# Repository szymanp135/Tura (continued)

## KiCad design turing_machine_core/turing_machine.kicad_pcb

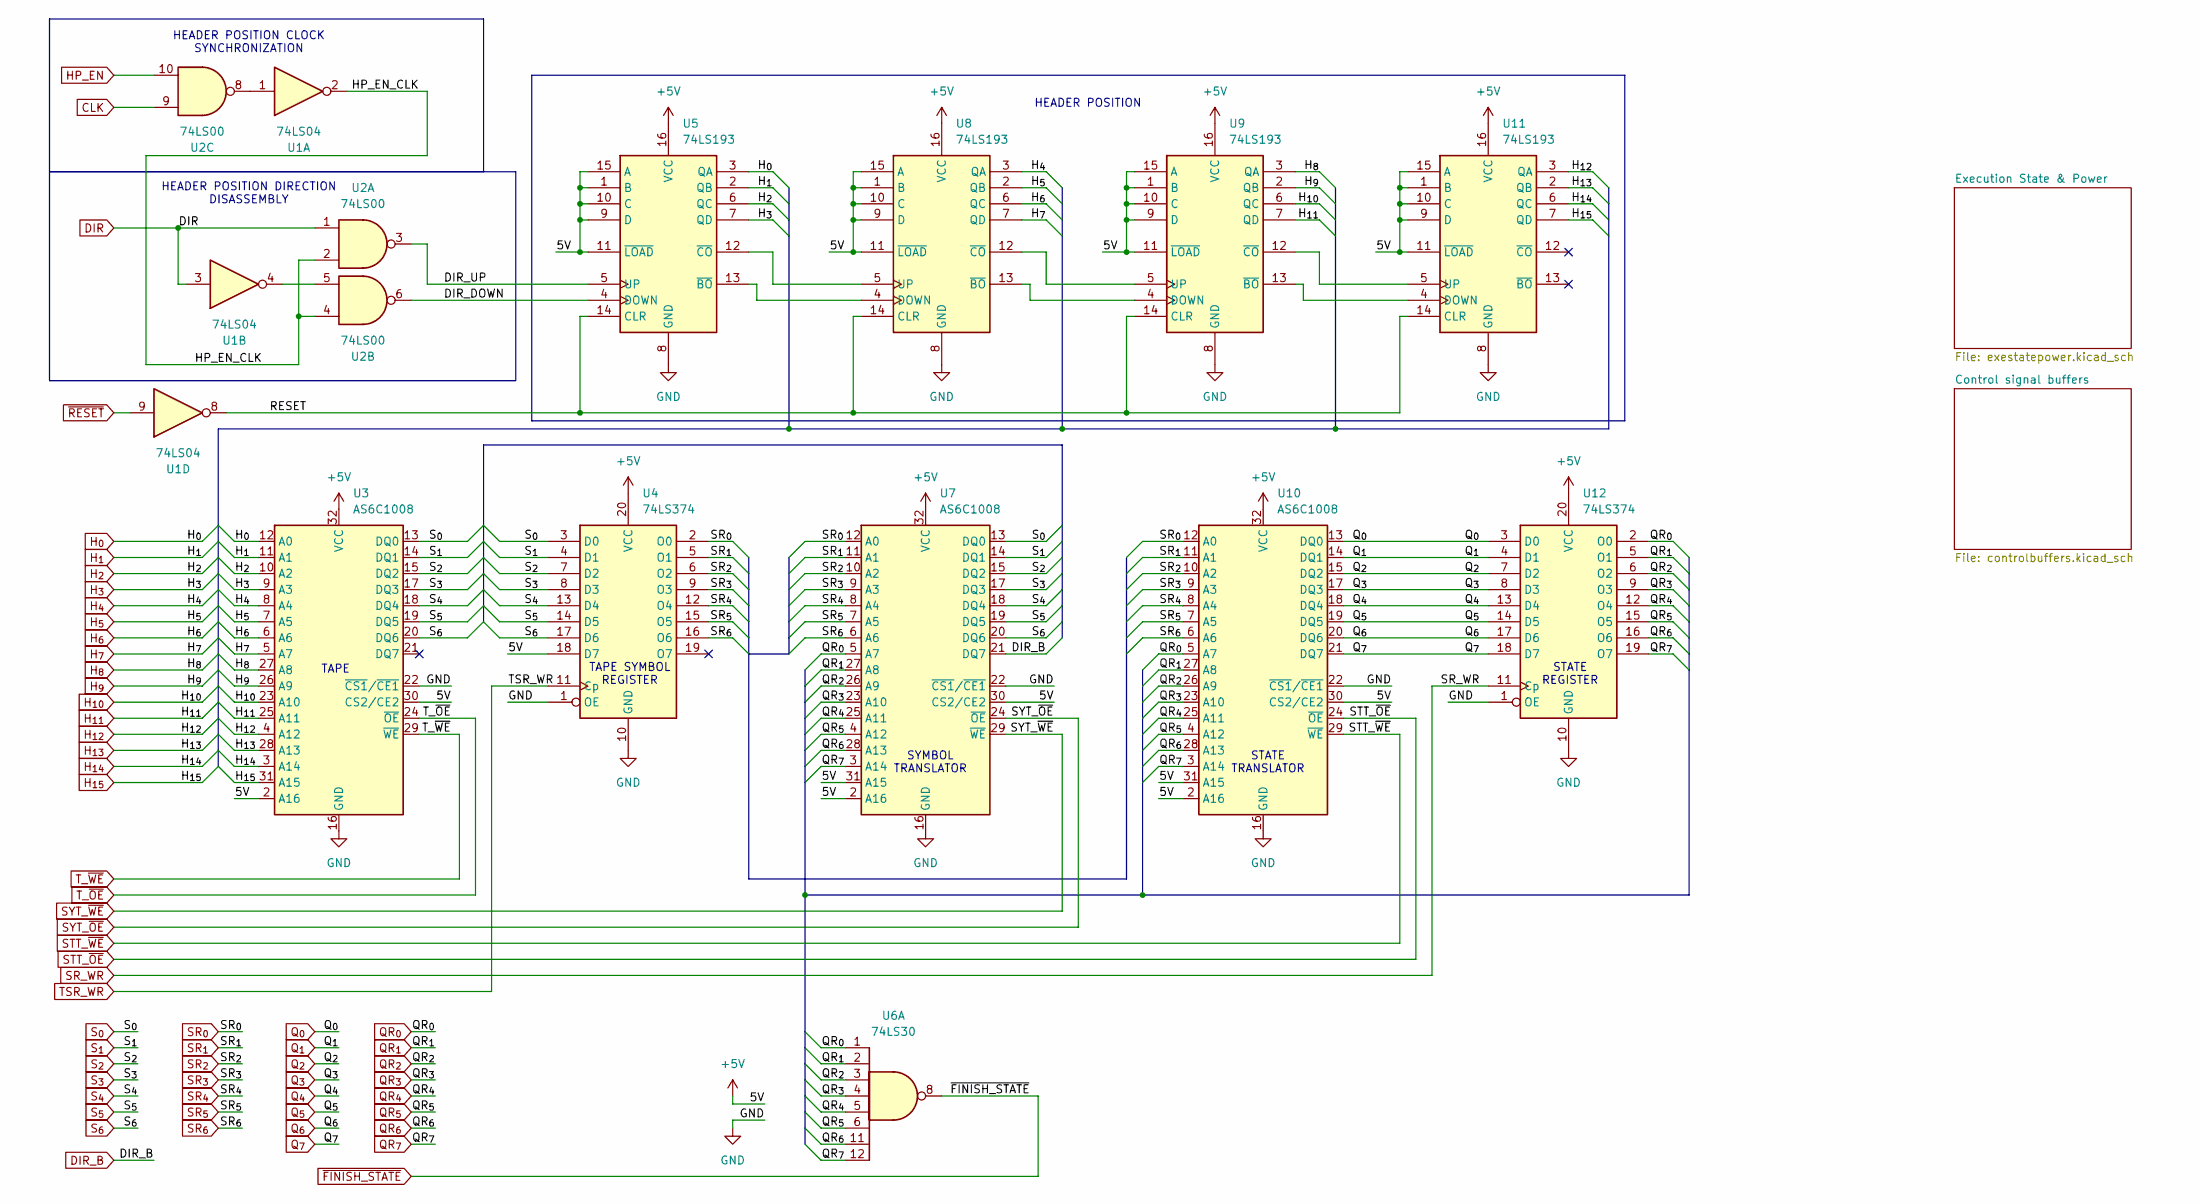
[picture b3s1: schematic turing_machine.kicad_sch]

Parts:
U1: 74LS04; DIP-14_W7.62mm
U2: 74LS00; DIP-14_W7.62mm
U3, U7, U10: AS6C1008; DIP-32_W15.24mm
U4, U12: 74LS374; DIP-20_W7.62mm
U5, U8, U9, U11: 74LS193; DIP-16_W7.62mm
U6: 74LS30; DIP-14_W7.62mm

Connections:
+5V: U3.2 (A16), U3.30 (CS2/CE2), U3.32 (VCC), U4.18 (D7), U4.20 (VCC), U5.1 (B), U5.9 (D), U5.10 (C), U5.11 (~LOAD), U5.15 (A), U5.16 (VCC), U7.2 (A16), U7.30 (CS2/CE2), U7.31 (A15), U7.32 (VCC), U8.1 (B), U8.9 (D), U8.10 (C), U8.11 (~LOAD), U8.15 (A), U8.16 (VCC), U9.1 (B), U9.9 (D), U9.10 (C), U9.11 (~LOAD), U9.15 (A), U9.16 (VCC), U10.2 (A16), U10.30 (CS2/CE2), U10.31 (A15), U10.32 (VCC), U11.1 (B), U11.9 (D), U11.10 (C), U11.11 (~LOAD), U11.15 (A), U11.16 (VCC), U12.20 (VCC); also elsewhere on the board
/DIR_DOWN: U2.6, U5.4 (DOWN)
/DIR_UP: U2.3, U5.5 (UP)
/HP_EN_CLK: U1.2, U2.2, U2.4
/RESET: U1.8, U5.14 (CLR), U8.14 (CLR), U9.14 (CLR), U11.14 (CLR)
CLK: U2.9; also elsewhere on the board
DIR: U1.3, U2.1; also elsewhere on the board
DIR_B: U7.21 (DQ7); also elsewhere on the board
GND: U3.16 (GND), U3.22 (~CS1/~CE1), U4.1 (OE), U4.10 (GND), U5.8 (GND), U7.16 (GND), U7.22 (~CS1/~CE1), U8.8 (GND), U9.8 (GND), U10.16 (GND), U10.22 (~CS1/~CE1), U11.8 (GND), U12.1 (OE), U12.10 (GND); also elsewhere on the board
HP_EN: U2.10, U4.11 (Cp); also elsewhere on the board
H_{0}: U3.12 (A0), U5.3 (QA); also elsewhere on the board
H_{1}: U3.11 (A1), U5.2 (QB); also elsewhere on the board
H_{2}: U3.10 (A2), U5.6 (QC); also elsewhere on the board
H_{3}: U3.9 (A3), U5.7 (QD); also elsewhere on the board
H_{4}: U3.8 (A4), U8.3 (QA); also elsewhere on the board
H_{5}: U3.7 (A5), U8.2 (QB); also elsewhere on the board
H_{6}: U3.6 (A6), U8.6 (QC); also elsewhere on the board
H_{7}: U3.5 (A7), U8.7 (QD); also elsewhere on the board
H_{8}: U3.27 (A8), U9.3 (QA); also elsewhere on the board
H_{9}: U3.26 (A9), U9.2 (QB); also elsewhere on the board
H_{10}: U3.23 (A10), U9.6 (QC); also elsewhere on the board
H_{11}: U3.25 (A11), U9.7 (QD); also elsewhere on the board
H_{12}: U3.4 (A12), U11.3 (QA); also elsewhere on the board
H_{13}: U3.28 (A13), U11.2 (QB); also elsewhere on the board
H_{14}: U3.3 (A14), U11.6 (QC); also elsewhere on the board
H_{15}: U3.31 (A15), U11.7 (QD); also elsewhere on the board
unnamed: U1.1, U2.8
unnamed: U1.4, U2.5
unnamed: U5.13 (~BO), U8.4 (DOWN)
unnamed: U5.12 (~CO), U8.5 (UP)
unnamed: U8.13 (~BO), U9.4 (DOWN)
unnamed: U8.12 (~CO), U9.5 (UP)
unnamed: U9.13 (~BO), U11.4 (DOWN)
unnamed: U9.12 (~CO), U11.5 (UP)
QR_{0}: U6.1, U7.5 (A7), U10.5 (A7), U12.2 (O0); also elsewhere on the board
QR_{1}: U6.2, U7.27 (A8), U10.27 (A8), U12.5 (O1); also elsewhere on the board
QR_{2}: U6.3, U7.26 (A9), U10.26 (A9), U12.6 (O2); also elsewhere on the board
QR_{3}: U6.4, U7.23 (A10), U10.23 (A10), U12.9 (O3); also elsewhere on the board
QR_{4}: U6.5, U7.25 (A11), U10.25 (A11), U12.12 (O4); also elsewhere on the board
QR_{5}: U6.6, U7.4 (A12), U10.4 (A12), U12.15 (O5); also elsewhere on the board
QR_{6}: U6.11, U7.28 (A13), U10.28 (A13), U12.16 (O6); also elsewhere on the board
QR_{7}: U6.12, U7.3 (A14), U10.3 (A14), U12.19 (O7); also elsewhere on the board
Q_{0}: U10.13 (DQ0), U12.3 (D0); also elsewhere on the board
Q_{1}: U10.14 (DQ1), U12.4 (D1); also elsewhere on the board
Q_{2}: U10.15 (DQ2), U12.7 (D2); also elsewhere on the board
Q_{3}: U10.17 (DQ3), U12.8 (D3); also elsewhere on the board
Q_{4}: U10.18 (DQ4), U12.13 (D4); also elsewhere on the board
Q_{5}: U10.19 (DQ5), U12.14 (D5); also elsewhere on the board
Q_{6}: U10.20 (DQ6), U12.17 (D6); also elsewhere on the board
Q_{7}: U10.21 (DQ7), U12.18 (D7); also elsewhere on the board
SR_WR: U12.11 (Cp); also elsewhere on the board
SR_{0}: U4.2 (O0), U7.12 (A0), U10.12 (A0); also elsewhere on the board
SR_{1}: U4.5 (O1), U7.11 (A1), U10.11 (A1); also elsewhere on the board
SR_{2}: U4.6 (O2), U7.10 (A2), U10.10 (A2); also elsewhere on the board
SR_{3}: U4.9 (O3), U7.9 (A3), U10.9 (A3); also elsewhere on the board
SR_{4}: U4.12 (O4), U7.8 (A4), U10.8 (A4); also elsewhere on the board
SR_{5}: U4.15 (O5), U7.7 (A5), U10.7 (A5); also elsewhere on the board
SR_{6}: U4.16 (O6), U7.6 (A6), U10.6 (A6); also elsewhere on the board
STT_~OE: U10.24 (~OE); also elsewhere on the board
STT_~WE: U10.29 (~WE); also elsewhere on the board
SYT_~OE: U7.24 (~OE); also elsewhere on the board
SYT_~WE: U7.29 (~WE); also elsewhere on the board
S_{0}: U3.13 (DQ0), U4.3 (D0), U7.13 (DQ0); also elsewhere on the board
S_{1}: U3.14 (DQ1), U4.4 (D1), U7.14 (DQ1); also elsewhere on the board
S_{2}: U3.15 (DQ2), U4.7 (D2), U7.15 (DQ2); also elsewhere on the board
S_{3}: U3.17 (DQ3), U4.8 (D3), U7.17 (DQ3); also elsewhere on the board
S_{4}: U3.18 (DQ4), U4.13 (D4), U7.18 (DQ4); also elsewhere on the board
S_{5}: U3.19 (DQ5), U4.14 (D5), U7.19 (DQ5); also elsewhere on the board
S_{6}: U3.20 (DQ6), U4.17 (D6), U7.20 (DQ6); also elsewhere on the board
T_~OE: U3.24 (~OE); also elsewhere on the board
T_~WE: U3.29 (~WE); also elsewhere on the board
~FINISH_STATE: U6.8; also elsewhere on the board
~RESET: U1.9; also elsewhere on the board

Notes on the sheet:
HEADER POSITION DIRECTION DISASSEMBLY
HEADER POSITION CLOCK SYNCHRONIZATION
STATE TRANSLATOR
TAPE SYMBOL REGISTER
HEADER POSITION
TAPE
STATE REGISTER
SYMBOL TRANSLATOR

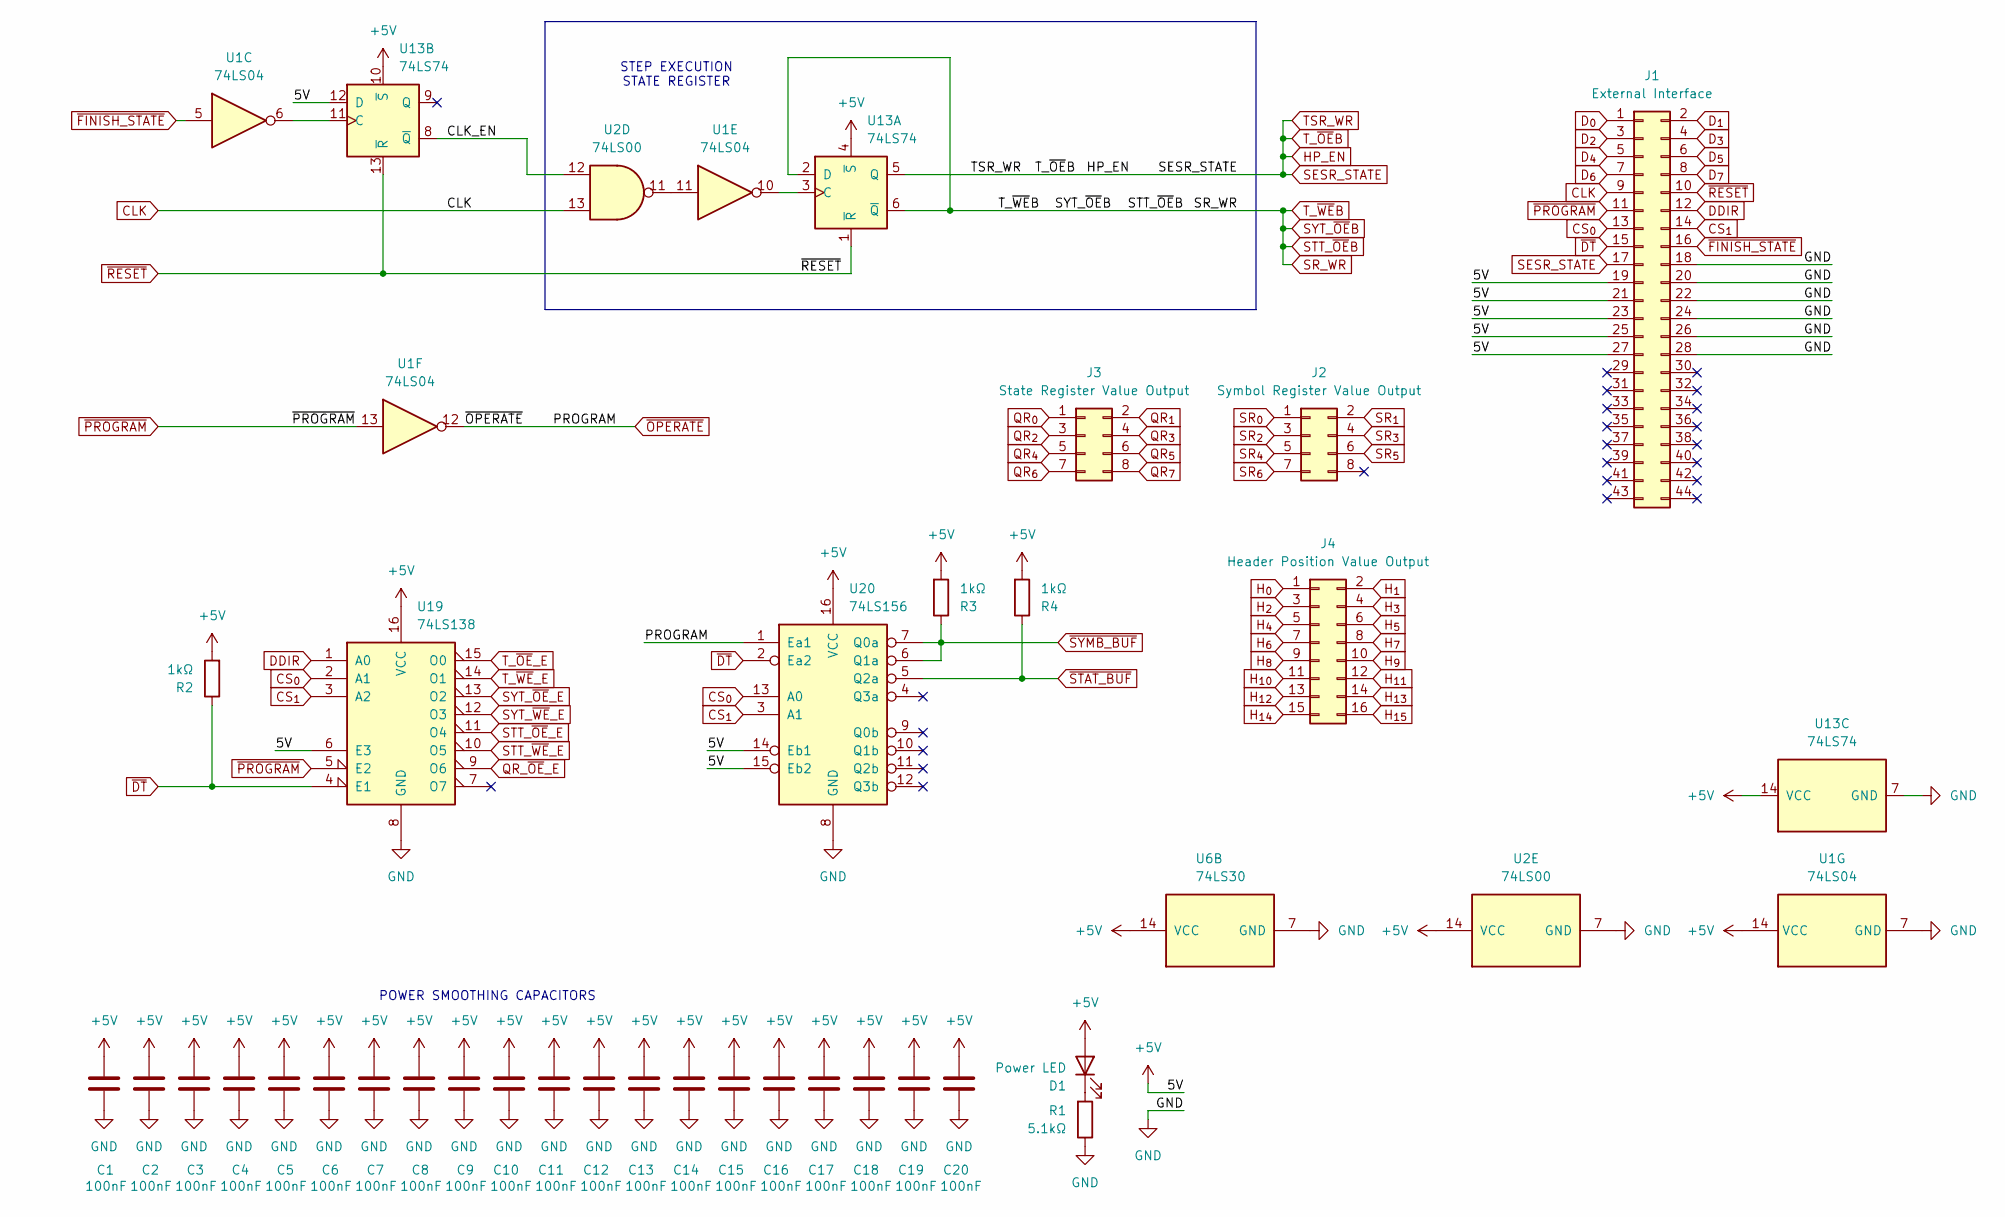
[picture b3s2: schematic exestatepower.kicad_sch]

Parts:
C1, C2, C3, C4, C5, C6, C7, C8, C9, C10, C11, C12, C13, C14, C15, C16, C17, C18, C19, C20: 100nF; C_Disc_D3.8mm_W2.6mm_P2.50mm
D1: Power LED; LED_D5.0mm
J1: External Interface; Connector_Edge_2x22pin_odd
J2: Symbol Register Value Output; PinHeader_2x04_P2.54mm_Vertical
J3: State Register Value Output; PinHeader_2x04_P2.54mm_Vertical
J4: Header Position Value Output; PinHeader_2x08_P2.54mm_Vertical
R1: 5.1kΩ; R_Axial_DIN0207_L6.3mm_D2.5mm_P10.16mm_Horizontal
R2, R3, R4: 1kΩ; R_Axial_DIN0207_L6.3mm_D2.5mm_P10.16mm_Horizontal
U1: 74LS04; DIP-14_W7.62mm
U2: 74LS00; DIP-14_W7.62mm
U6: 74LS30; DIP-14_W7.62mm
U13: 74LS74; DIP-14_W7.62mm
U19: 74LS138; DIP-16_W7.62mm
U20: 74LS156; DIP-16_W7.62mm

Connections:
+5V: C1.1, C2.1, C3.1, C4.1, C5.1, C6.1, C7.1, C8.1, C9.1, C10.1, C11.1, C12.1, C13.1, C14.1, C15.1, C16.1, C17.1, C18.1, C19.1, C20.1, D1.2 (A), J1.19, J1.21, J1.23, J1.25, J1.27, R2.2, R3.2, R4.2, U1.14 (VCC), U2.14 (VCC), U6.14 (VCC), U13.4 (~S), U13.10 (~S), U13.12 (D), U13.14 (VCC), U19.6 (E3), U19.16 (VCC), U20.14 (Eb1), U20.15 (Eb2), U20.16 (VCC); also elsewhere on the board
/Execution State & Power/CLK_EN: U2.12, U13.8 (~Q)
CLK: J1.9, U2.13; also elsewhere on the board
CS_{0}: J1.13, U19.2 (A1), U20.13 (A0)
CS_{1}: J1.14, U19.3 (A2), U20.3 (A1)
DDIR: J1.12, U19.1 (A0); also elsewhere on the board
D_{0}: J1.1; also elsewhere on the board
D_{1}: J1.2; also elsewhere on the board
D_{2}: J1.3; also elsewhere on the board
D_{3}: J1.4; also elsewhere on the board
D_{4}: J1.5; also elsewhere on the board
D_{5}: J1.6; also elsewhere on the board
D_{6}: J1.7; also elsewhere on the board
D_{7}: J1.8; also elsewhere on the board
GND: C1.2, C2.2, C3.2, C4.2, C5.2, C6.2, C7.2, C8.2, C9.2, C10.2, C11.2, C12.2, C13.2, C14.2, C15.2, C16.2, C17.2, C18.2, C19.2, C20.2, J1.18, J1.20, J1.22, J1.24, J1.26, J1.28, R1.1, U1.7 (GND), U2.7 (GND), U6.7 (GND), U13.7 (GND), U19.8 (GND), U20.8 (GND); also elsewhere on the board
HP_EN: J1.17, U13.5 (Q); also elsewhere on the board
H_{0}: J4.1; also elsewhere on the board
H_{1}: J4.2; also elsewhere on the board
H_{2}: J4.3; also elsewhere on the board
H_{3}: J4.4; also elsewhere on the board
H_{4}: J4.5; also elsewhere on the board
H_{5}: J4.6; also elsewhere on the board
H_{6}: J4.7; also elsewhere on the board
H_{7}: J4.8; also elsewhere on the board
H_{8}: J4.9; also elsewhere on the board
H_{9}: J4.10; also elsewhere on the board
H_{10}: J4.11; also elsewhere on the board
H_{11}: J4.12; also elsewhere on the board
H_{12}: J4.13; also elsewhere on the board
H_{13}: J4.14; also elsewhere on the board
H_{14}: J4.15; also elsewhere on the board
H_{15}: J4.16; also elsewhere on the board
unnamed: D1.1 (K), R1.2
unnamed: U1.11, U2.11
unnamed: U1.10, U13.3 (C)
unnamed: U1.6, U13.11 (C)
QR_{0}: J3.1; also elsewhere on the board
QR_{1}: J3.2; also elsewhere on the board
QR_{2}: J3.3; also elsewhere on the board
QR_{3}: J3.4; also elsewhere on the board
QR_{4}: J3.5; also elsewhere on the board
QR_{5}: J3.6; also elsewhere on the board
QR_{6}: J3.7; also elsewhere on the board
QR_{7}: J3.8; also elsewhere on the board
QR_~OE_E: U19.9 (O6); also elsewhere on the board
SR_WR: U13.2 (D), U13.6 (~Q); also elsewhere on the board
SR_{0}: J2.1; also elsewhere on the board
SR_{1}: J2.2; also elsewhere on the board
SR_{2}: J2.3; also elsewhere on the board
SR_{3}: J2.4; also elsewhere on the board
SR_{4}: J2.5; also elsewhere on the board
SR_{5}: J2.6; also elsewhere on the board
SR_{6}: J2.7; also elsewhere on the board
STT_~OE_E: U19.11 (O4); also elsewhere on the board
STT_~WE_E: U19.10 (O5); also elsewhere on the board
SYT_~OE_E: U19.13 (O2); also elsewhere on the board
SYT_~WE_E: U19.12 (O3); also elsewhere on the board
T_~OE_E: U19.15 (O0); also elsewhere on the board
T_~WE_E: U19.14 (O1); also elsewhere on the board
~DT: J1.15, R2.1, U19.4 (E1), U20.2 (Ea2)
~FINISH_STATE: J1.16, U1.5; also elsewhere on the board
~OPERATE: U1.12, U20.1 (Ea1); also elsewhere on the board
~PROGRAM: J1.11, U1.13, U19.5 (E2); also elsewhere on the board
~RESET: J1.10, U13.1 (~R), U13.13 (~R); also elsewhere on the board
~STAT_BUF: R4.1, U20.5 (Q2a); also elsewhere on the board
~SYMB_BUF: R3.1, U20.6 (Q1a), U20.7 (Q0a); also elsewhere on the board

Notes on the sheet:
STEP EXECUTION STATE REGISTER
POWER SMOOTHING CAPACITORS

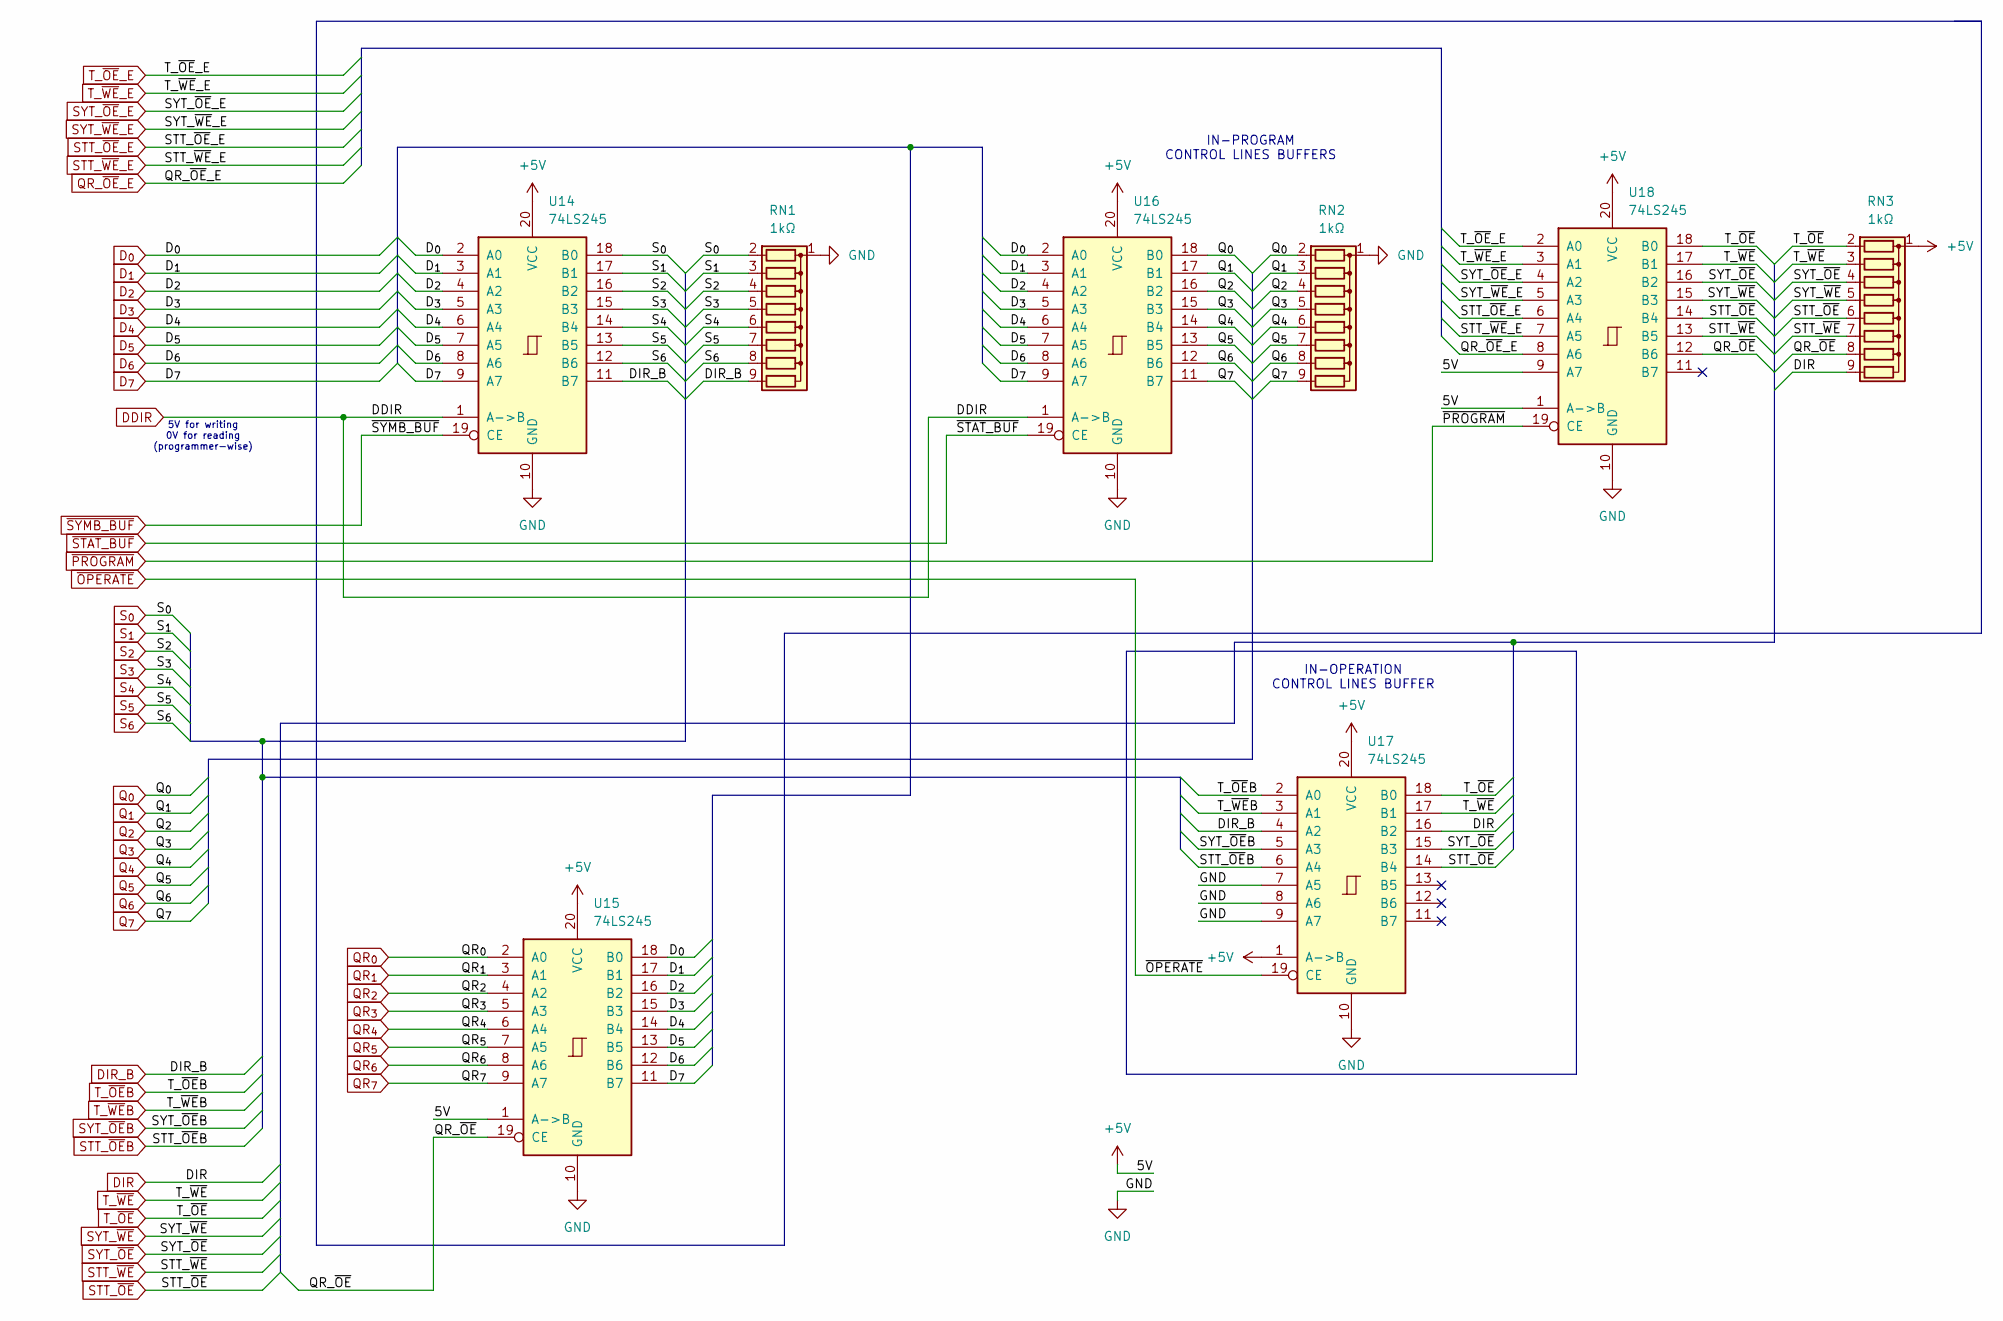
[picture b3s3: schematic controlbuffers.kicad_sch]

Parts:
RN1, RN2, RN3: 1kΩ; R_Array_SIP9
U14, U15, U16, U17, U18: 74LS245; DIP-20_W7.62mm

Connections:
+5V: RN3.1 (common), U14.20 (VCC), U15.1 (A->B), U15.20 (VCC), U16.20 (VCC), U17.1 (A->B), U17.20 (VCC), U18.1 (A->B), U18.9 (A7), U18.20 (VCC); also elsewhere on the board
/Control signal buffers/QR_~OE: RN3.8 (R7), U15.19 (CE), U18.12 (B6)
DDIR: U14.1 (A->B), U16.1 (A->B); also elsewhere on the board
DIR: RN3.9 (R8), U17.16 (B2); also elsewhere on the board
DIR_B: RN1.9 (R8), U14.11 (B7), U17.4 (A2); also elsewhere on the board
D_{0}: U14.2 (A0), U15.18 (B0), U16.2 (A0); also elsewhere on the board
D_{1}: U14.3 (A1), U15.17 (B1), U16.3 (A1); also elsewhere on the board
D_{2}: U14.4 (A2), U15.16 (B2), U16.4 (A2); also elsewhere on the board
D_{3}: U14.5 (A3), U15.15 (B3), U16.5 (A3); also elsewhere on the board
D_{4}: U14.6 (A4), U15.14 (B4), U16.6 (A4); also elsewhere on the board
D_{5}: U14.7 (A5), U15.13 (B5), U16.7 (A5); also elsewhere on the board
D_{6}: U14.8 (A6), U15.12 (B6), U16.8 (A6); also elsewhere on the board
D_{7}: U14.9 (A7), U15.11 (B7), U16.9 (A7); also elsewhere on the board
GND: RN1.1 (common), RN2.1 (common), U14.10 (GND), U15.10 (GND), U16.10 (GND), U17.7 (A5), U17.8 (A6), U17.9 (A7), U17.10 (GND), U18.10 (GND); also elsewhere on the board
HP_EN: U17.2 (A0); also elsewhere on the board
QR_{0}: U15.2 (A0); also elsewhere on the board
QR_{1}: U15.3 (A1); also elsewhere on the board
QR_{2}: U15.4 (A2); also elsewhere on the board
QR_{3}: U15.5 (A3); also elsewhere on the board
QR_{4}: U15.6 (A4); also elsewhere on the board
QR_{5}: U15.7 (A5); also elsewhere on the board
QR_{6}: U15.8 (A6); also elsewhere on the board
QR_{7}: U15.9 (A7); also elsewhere on the board
QR_~OE_E: U18.8 (A6); also elsewhere on the board
Q_{0}: RN2.2 (R1), U16.18 (B0); also elsewhere on the board
Q_{1}: RN2.3 (R2), U16.17 (B1); also elsewhere on the board
Q_{2}: RN2.4 (R3), U16.16 (B2); also elsewhere on the board
Q_{3}: RN2.5 (R4), U16.15 (B3); also elsewhere on the board
Q_{4}: RN2.6 (R5), U16.14 (B4); also elsewhere on the board
Q_{5}: RN2.7 (R6), U16.13 (B5); also elsewhere on the board
Q_{6}: RN2.8 (R7), U16.12 (B6); also elsewhere on the board
Q_{7}: RN2.9 (R8), U16.11 (B7); also elsewhere on the board
SR_WR: U17.3 (A1), U17.5 (A3), U17.6 (A4); also elsewhere on the board
STT_~OE: RN3.6 (R5), U17.14 (B4), U18.14 (B4); also elsewhere on the board
STT_~OE_E: U18.6 (A4); also elsewhere on the board
STT_~WE: RN3.7 (R6), U18.13 (B5); also elsewhere on the board
STT_~WE_E: U18.7 (A5); also elsewhere on the board
SYT_~OE: RN3.4 (R3), U17.15 (B3), U18.16 (B2); also elsewhere on the board
SYT_~OE_E: U18.4 (A2); also elsewhere on the board
SYT_~WE: RN3.5 (R4), U18.15 (B3); also elsewhere on the board
SYT_~WE_E: U18.5 (A3); also elsewhere on the board
S_{0}: RN1.2 (R1), U14.18 (B0); also elsewhere on the board
S_{1}: RN1.3 (R2), U14.17 (B1); also elsewhere on the board
S_{2}: RN1.4 (R3), U14.16 (B2); also elsewhere on the board
S_{3}: RN1.5 (R4), U14.15 (B3); also elsewhere on the board
S_{4}: RN1.6 (R5), U14.14 (B4); also elsewhere on the board
S_{5}: RN1.7 (R6), U14.13 (B5); also elsewhere on the board
S_{6}: RN1.8 (R7), U14.12 (B6); also elsewhere on the board
T_~OE: RN3.2 (R1), U17.18 (B0), U18.18 (B0); also elsewhere on the board
T_~OE_E: U18.2 (A0); also elsewhere on the board
T_~WE: RN3.3 (R2), U17.17 (B1), U18.17 (B1); also elsewhere on the board
T_~WE_E: U18.3 (A1); also elsewhere on the board
~OPERATE: U17.19 (CE); also elsewhere on the board
~PROGRAM: U18.19 (CE); also elsewhere on the board
~STAT_BUF: U16.19 (CE); also elsewhere on the board
~SYMB_BUF: U14.19 (CE); also elsewhere on the board

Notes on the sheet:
IN-OPERATION CONTROL LINES BUFFER
IN-PROGRAM CONTROL LINES BUFFERS
5V for writing 0V for reading (programmer-wise)

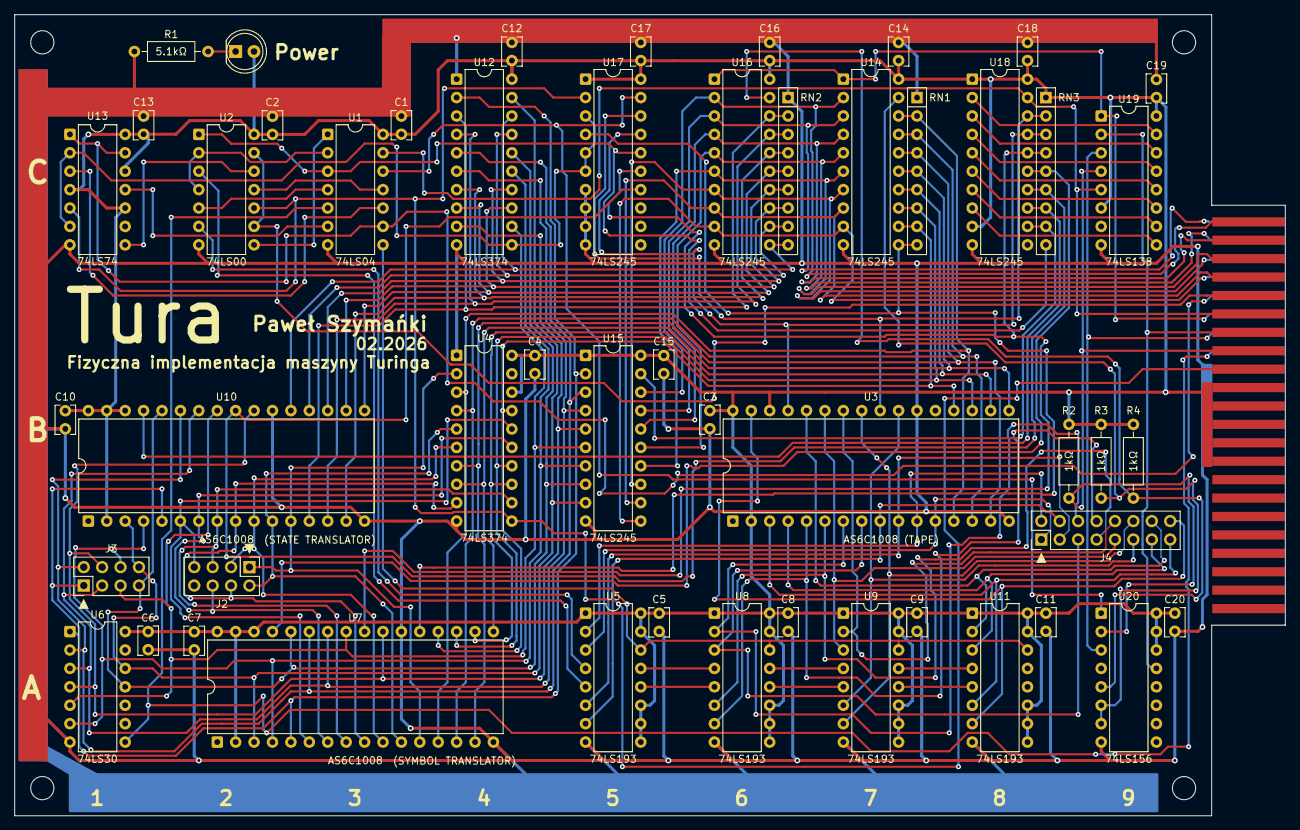
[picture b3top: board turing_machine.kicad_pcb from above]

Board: 2 copper layers, 175.3 x 110.5 mm, 52 parts (0 on the bottom side), 102 nets.

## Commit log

2026-02-06 init commit
2026-02-06 added documentation (wip)
2026-02-06 PCB layout planning and further documantation work
2026-02-06 finished PCB planning
2026-02-07 fixed schematics bugs and updated documentation
2026-02-07 removed unnecessary files
2026-02-07 adjusted PCB design for schematic fixes
2026-02-07 added edge connector to PCB
2026-02-07 small border ground plane adjustments and added backside logos
2026-02-07 small cosmetic PCB changes
2026-02-08 further documentation work (programming procedure desctiption)
2026-02-08 further work on programming section in documentation
2026-02-08 finished programming part of documentation and added other cosmetic changes to it
2026-02-08 added execution and result retrieval descriptions to documentation
2026-02-08 added two connectors to schematics and PCB design and reformatted slightly documentation
2026-02-08 moved Header Position output from main connector to dedicated one and updated documentation for that
2026-02-11 added driver
2026-02-14 added control panel and moved LEDs to it
2026-02-15 finished driver PCB layout
2026-02-20 added some wiring and fixed few schematic bugs
2026-02-20 finished driver PCB wiring and added some marks
2026-02-21 added few markings to PCBs
2026-02-22 added backplane
2026-03-20 added github links to core and driver boards
2026-03-20 added backplane PCB and adjusted driver silkscreen text thickness
